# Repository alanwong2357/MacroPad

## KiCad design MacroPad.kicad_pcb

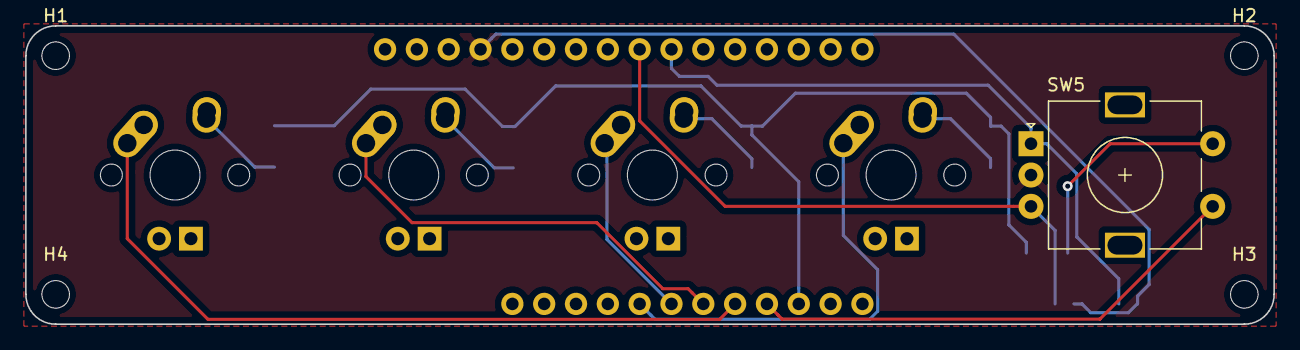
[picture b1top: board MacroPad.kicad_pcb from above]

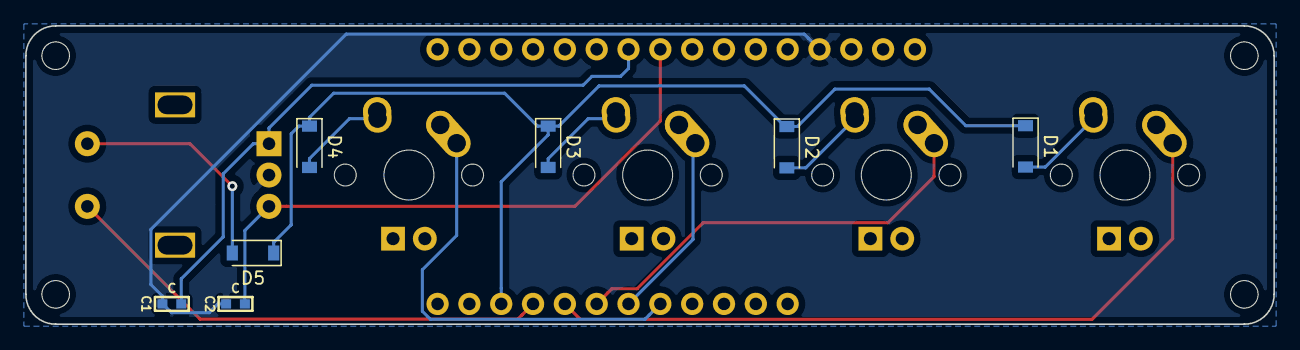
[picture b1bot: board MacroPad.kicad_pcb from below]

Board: 2 copper layers, 99.6 x 23.8 mm, 17 parts (8 on the bottom side), 14 nets.

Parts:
C1, C2: C; C_0603
D1, D2, D3, D4, D5: D; D_SOD-123
H1, H2, H3, H4: MountingHole; MountingHole_2.2mm_M2
MS1: FEATHERWING_NODIM
SW1, SW2, SW3, SW4: SW_Push; MX-1U
SW5: Rotary_Encoder_Switch; RotaryEncoder_Alps_EC11E-Switch_Vertical_H20mm

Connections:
Col1: MS1.20, SW5.S1
Col2: MS1.21, SW1.1
Col3: MS1.22, SW2.1
Col4: MS1.23, SW3.1
Col5: MS1.24, SW4.1
GND: C1.1, C2.1, MS1.4, SW5.C
unnamed: D1.2, SW1.2
unnamed: D2.2, SW2.2
unnamed: D3.2, SW3.2
unnamed: D4.2, SW4.2
unnamed: D5.2, SW5.S2
RotA: C1.2, MS1.10, SW5.A
RotB: C2.2, MS1.9, SW5.B
Row1: D1.1, D2.1, D3.1, D4.1, D5.1, MS1.19

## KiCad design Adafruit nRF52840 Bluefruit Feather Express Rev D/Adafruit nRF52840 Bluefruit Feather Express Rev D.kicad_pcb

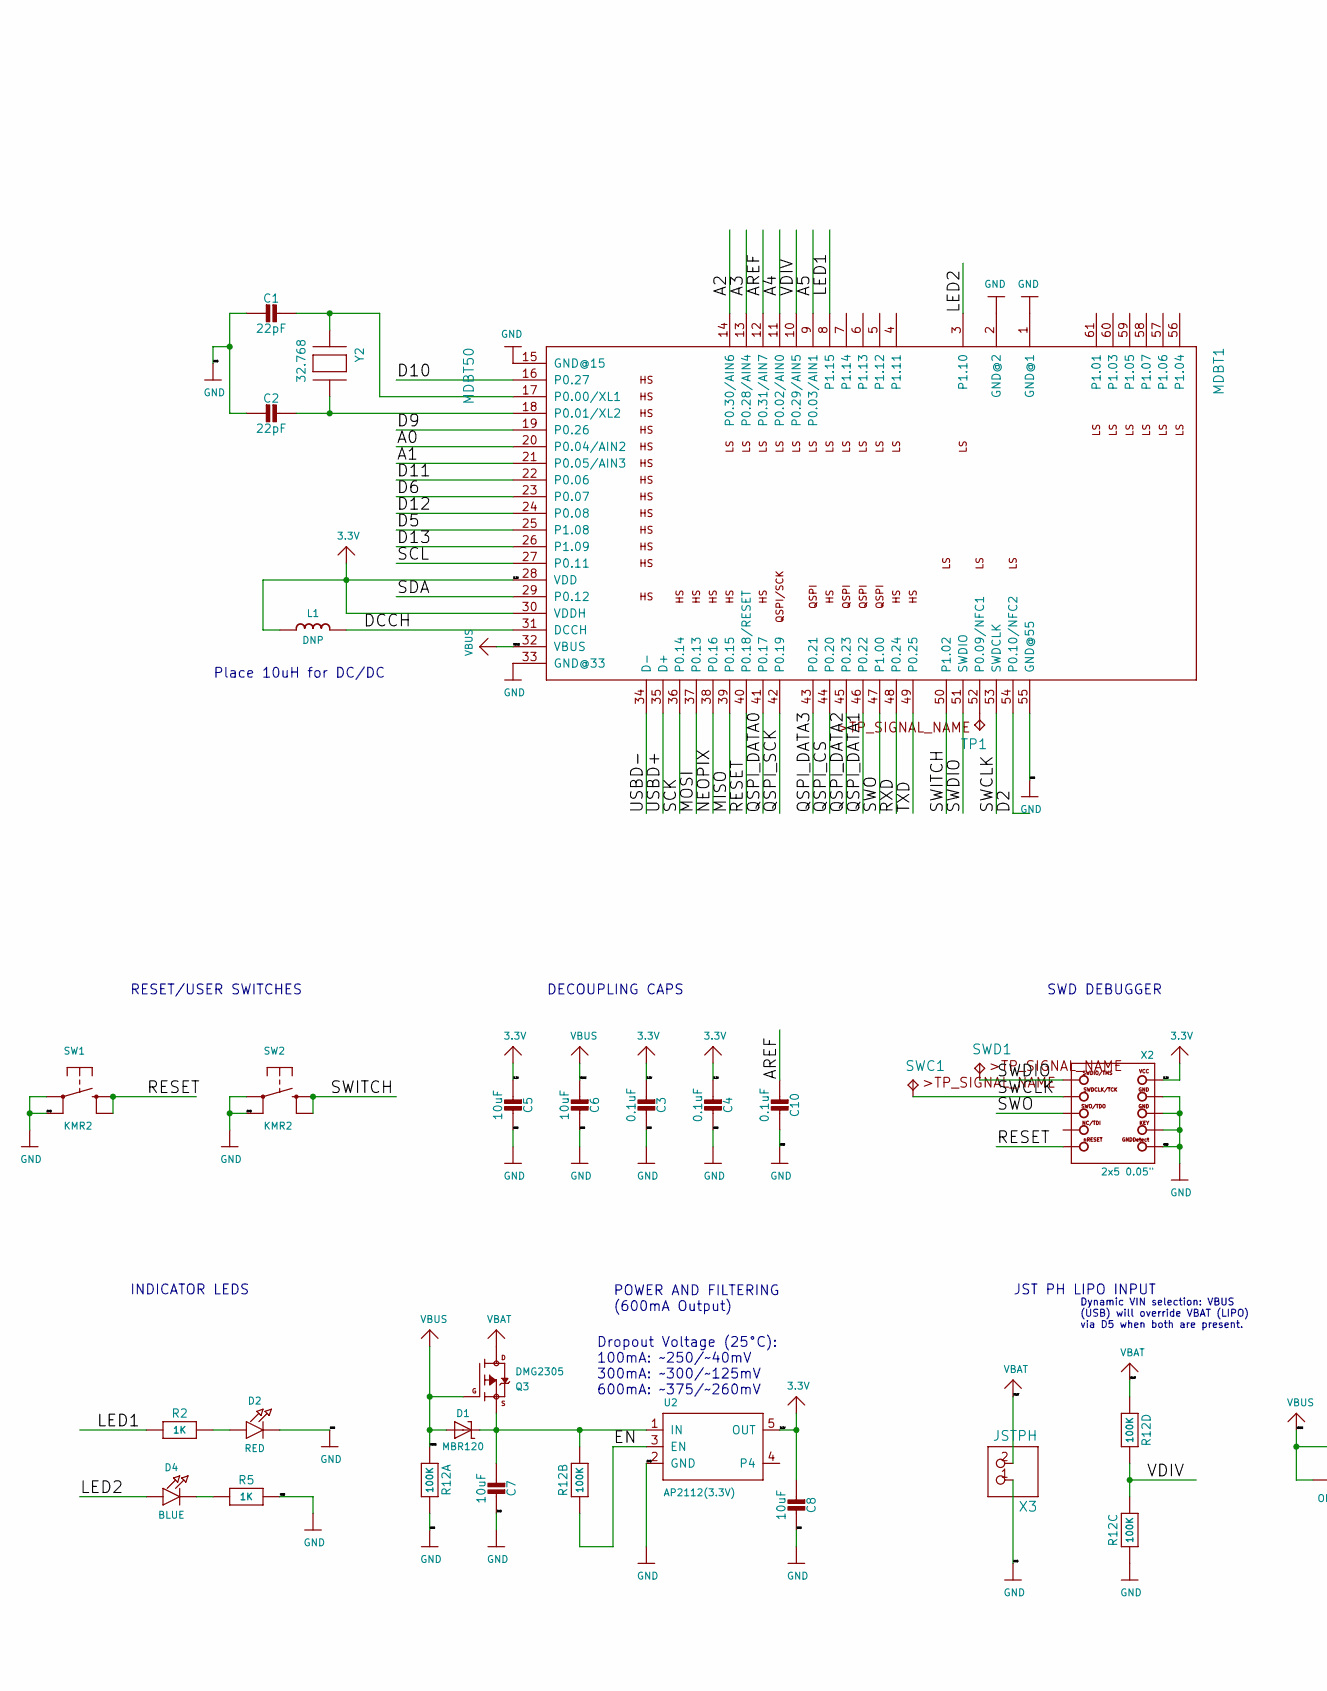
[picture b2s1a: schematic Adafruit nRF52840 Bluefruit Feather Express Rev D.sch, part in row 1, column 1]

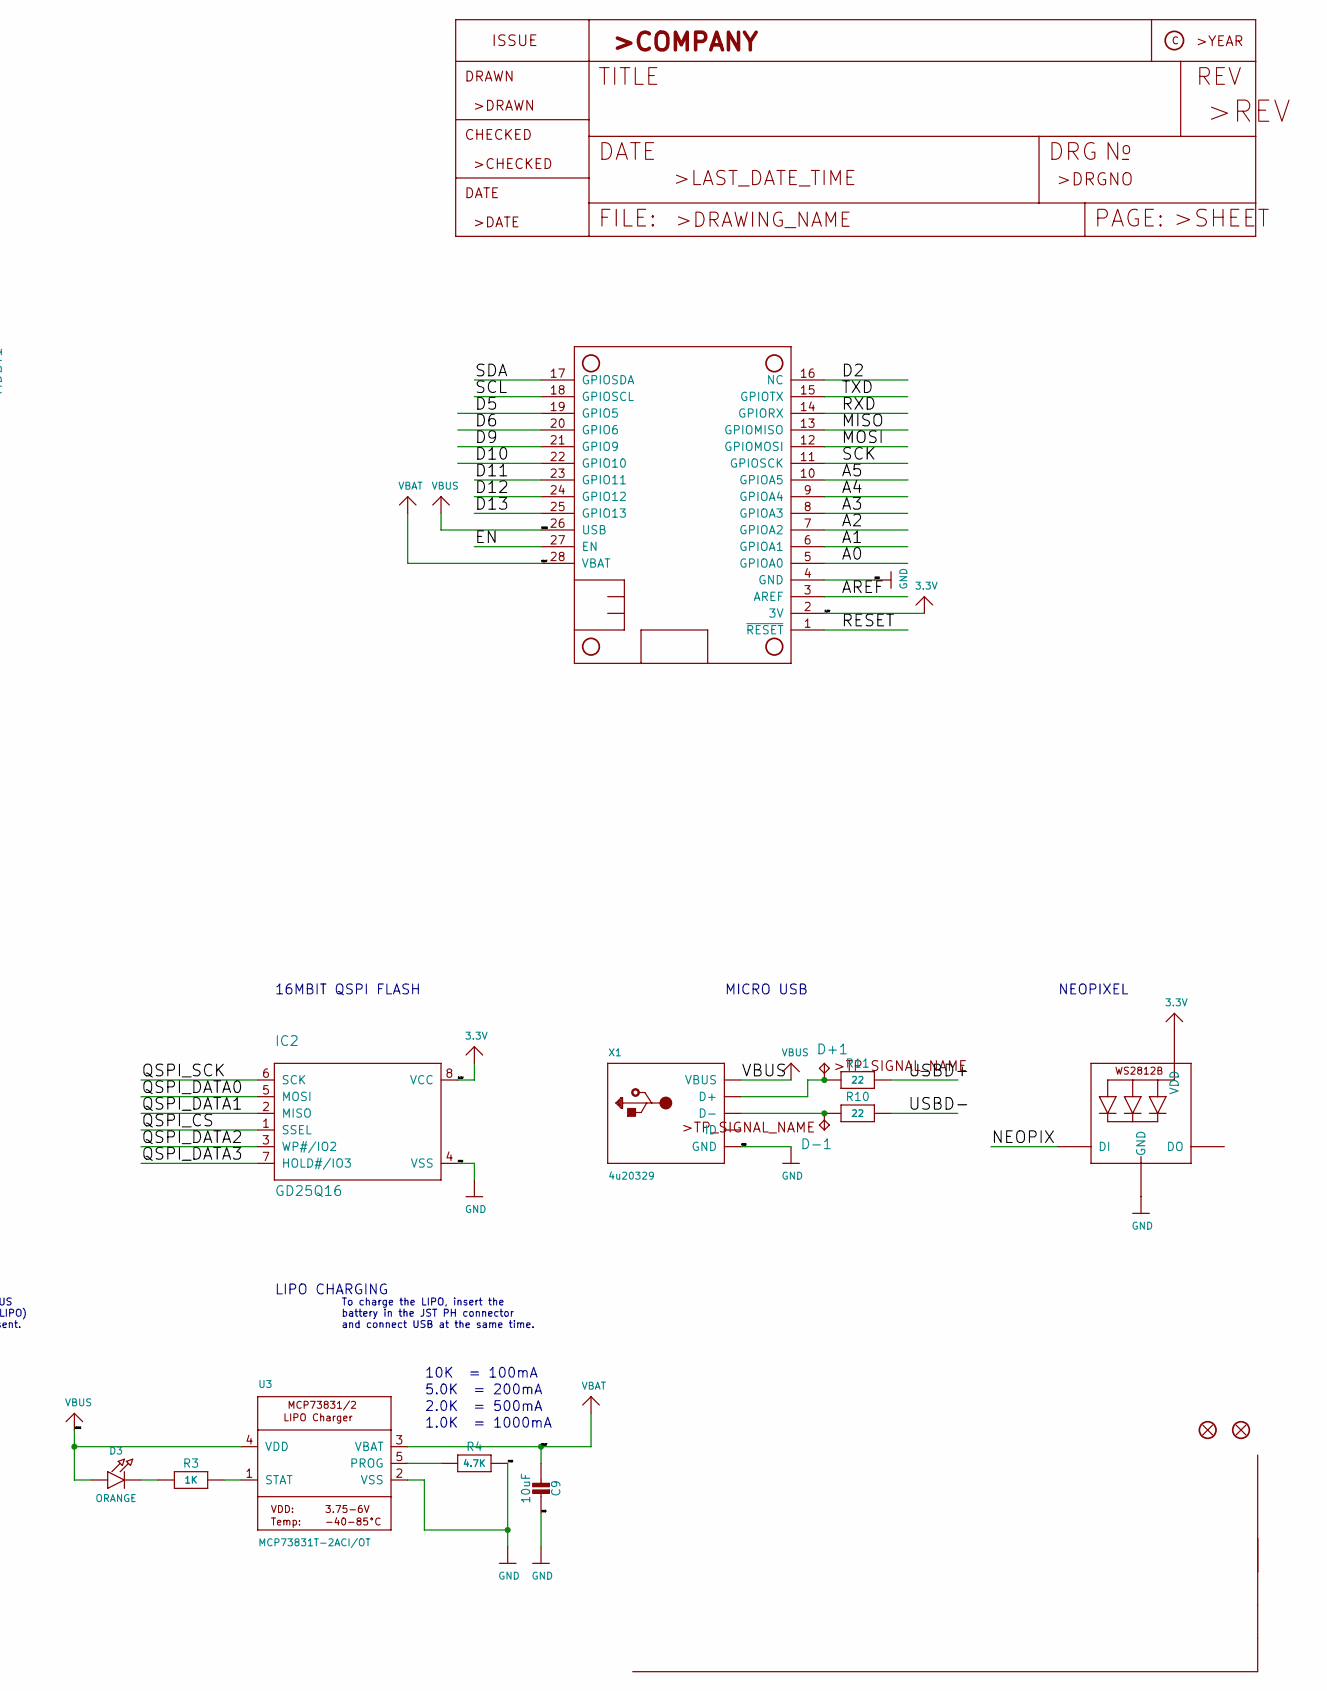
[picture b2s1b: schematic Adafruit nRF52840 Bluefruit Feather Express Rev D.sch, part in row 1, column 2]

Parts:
C1, C2: 22pF; 0603-NO
C3, C4, C10: 0.1uF; 0603-NO
C5, C6, C7, C8, C9: 10uF; 0805-NO
D1: MBR120; SOD-123
D2: RED; CHIPLED_0805_NOOUTLINE
D3: ORANGE; CHIPLED_0805_NOOUTLINE
D4: BLUE; CHIPLED_0805_NOOUTLINE
D+1: TPTP10R; TP10R
D-1: TPTP10R; TP10R
FID1, FID2: FIDUCIAL_1MM
IC2: GD25Q16; USON8
L1: DNP; _0805MP
LED1: WS2812B3535; LED3535
MDBT1: MDBT50
MS1: FEATHERWING_NODIM
Q3: DMG2305; SOT23-R
R2, R3, R5: 1K; 0603-NO
R4: 4.7K; 0603-NO
R10, R11: 22; 0603-NO
R12: 100K; RESPACK_4X0603
SW1, SW2: KMR2; BTN_KMR2_4.6X2.8
SWC1: TPTP12R; TP12R
SWD1: TPTP12R; TP12R
TP1: TPTP10R; TP10R
U2: AP2112(3.3V); SOT23-5
U3: MCP73831T-2ACI/OT; SOT23-5
X1: 4u20329; 4UCONN_20329_V2
X2: 2x5 0.05\"; 2X05_1.27MM_BOX_POSTS
X3: JSTPH; JSTPH2
Y2: 32.768; XTAL3215

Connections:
3.3V: C3.2, C4.2, C5.2, C8.2, IC2.8 (VCC), L1.1, LED1.2 (VDD), MDBT1.28 (VDD), MDBT1.30 (VDDH), MS1.2 (3V), U2.5 (OUT), X2.1 (VCC)
/A0: MDBT1.20 (P0.04/AIN2), MS1.5 (GPIOA0)
/A1: MDBT1.21 (P0.05/AIN3), MS1.6 (GPIOA1)
/A2: MDBT1.14 (P0.30/AIN6), MS1.7 (GPIOA2)
/A3: MDBT1.13 (P0.28/AIN4), MS1.8 (GPIOA3)
/A4: MDBT1.11 (P0.02/AIN0), MS1.9 (GPIOA4)
/A5: MDBT1.9 (P0.03/AIN1), MS1.10 (GPIOA5)
/AREF: C10.2, MDBT1.12 (P0.31/AIN7), MS1.3 (AREF)
/D2: MDBT1.54 (P0.10/NFC2), MS1.16 (NC)
/D5: MDBT1.25 (P1.08), MS1.19 (GPIO5)
/D6: MDBT1.23 (P0.07), MS1.20 (GPIO6)
/D9: MDBT1.19 (P0.26), MS1.21 (GPIO9)
/D10: MDBT1.16 (P0.27), MS1.22 (GPIO10)
/D11: MDBT1.22 (P0.06), MS1.23 (GPIO11)
/D12: MDBT1.24 (P0.08), MS1.24 (GPIO12)
/D13: MDBT1.26 (P1.09), MS1.25 (GPIO13)
/DCCH: L1.2, MDBT1.31 (DCCH)
/EN: MS1.27 (EN), R12.2 (1), U2.3 (EN)
/LED1: MDBT1.8 (P1.15), R2.1
/LED2: D4.A, MDBT1.3 (P1.10)
/MISO: MDBT1.39 (P0.15), MS1.13 (GPIOMISO)
/MOSI: MDBT1.37 (P0.13), MS1.12 (GPIOMOSI)
/NEOPIX: LED1.1 (DI), MDBT1.38 (P0.16)
/QSPI_CS: IC2.1 (SSEL), MDBT1.44 (P0.20)
/QSPI_DATA0: IC2.5 (MOSI), MDBT1.41 (P0.17)
/QSPI_DATA1: IC2.2 (MISO), MDBT1.46 (P0.22)
/QSPI_DATA2: IC2.3 (WP#/IO2), MDBT1.45 (P0.23)
/QSPI_DATA3: IC2.7 (HOLD#/IO3), MDBT1.43 (P0.21)
/QSPI_SCK: IC2.6 (SCK), MDBT1.42 (P0.19)
/RESET: MDBT1.40 (P0.18/RESET), MS1.1 (~RESET), SW1.B (S), SW1.B' (S1), X2.10 (NRESET)
/RXD: MDBT1.48 (P0.24), MS1.14 (GPIORX)
/SCK: MDBT1.36 (P0.14), MS1.11 (GPIOSCK)
/SCL: MDBT1.27 (P0.11), MS1.18 (GPIOSCL)
/SDA: MDBT1.29 (P0.12), MS1.17 (GPIOSDA)
/SWCLK: MDBT1.53 (SWDCLK), SWC1.TP, X2.4 (SWDCLK)
/SWDIO: MDBT1.51 (SWDIO), SWD1.TP, X2.2 (SWDIO)
/SWITCH: MDBT1.50 (P1.02), SW2.B (S), SW2.B' (S1)
/SWO: MDBT1.47 (P1.00), X2.6 (SWO)
/TXD: MDBT1.49 (P0.25), MS1.15 (GPIOTX)
/USBD+: MDBT1.35 (D+), R11.2
/USBD-: MDBT1.34 (D-), R10.2
/VDIV: MDBT1.10 (P0.29/AIN5), R12.5 (2), R12.6 (2)
GND: C1.2, C2.2, C3.1, C4.1, C5.1, C6.1, C7.1, C8.1, C9.1, C10.1, D2.C, IC2.4 (VSS), LED1.4 (GND), MDBT1.1 (GND@1), MDBT1.2 (GND@2), MDBT1.15 (GND@15), MDBT1.33 (GND@33), MDBT1.55 (GND@55), MS1.4 (GND), R4.2, R5.2, R12.3 (1), R12.8 (2), SW1.A, SW1.A' (P1), SW2.A, SW2.A' (P1), U2.2 (GND), U3.2 (VSS), X1.BASE@1 (GND), X1.BASE@2 (GND), X1.GND, X1.SPRT@1 (GND), X1.SPRT@2 (GND), X1.SPRT@3 (GND), X1.SPRT@4 (GND), X2.3 (GND@1), X2.5 (GND@2), X2.7 (KEY), X2.9 (GNDDETECT), X3.1
unnamed: C1.1, MDBT1.17 (P0.00/XL1), Y2.P$1
unnamed: C2.1, MDBT1.18 (P0.01/XL2), Y2.P$2
unnamed: C7.2, D1.C, Q3.2 (S), R12.7 (2), U2.1 (IN)
unnamed: D2.A, R2.2
unnamed: D3.C, R3.1
unnamed: D4.C, R5.1
unnamed: D+1.TP, R11.1, X1.D+
unnamed: D-1.TP, R10.1, X1.D-
unnamed: MDBT1.52 (P0.09/NFC1), TP1.TP
unnamed: R3.2, U3.1 (STAT)
unnamed: R4.1, U3.5 (PROG)
VBAT: C9.2, MS1.28 (VBAT), Q3.3 (D), R12.4 (1), U3.3 (VBAT), X3.2
VBUS: C6.2, D1.A, D3.A, MDBT1.32 (VBUS), MS1.26 (USB), Q3.1 (G), R12.1, U3.4 (VDD), X1.VBUS

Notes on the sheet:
10K = 100mA
5.0K = 200mA
2.0K = 500mA
1.0K = 1000mA
LIPO CHARGING
To charge the LIPO, insert the battery in the JST PH connector and connect USB at the same time.
POWER AND FILTERING (600mA Output)
JST PH LIPO INPUT
Dynamic VIN selection: VBUS (USB) will override VBAT (LIPO) via D5 when both are present.
Dropout Voltage (25°C): 100mA: ~~250/~~40mV 300mA: ~~300/~~125mV 600mA: ~~375/~~260mV
INDICATOR LEDS
RESET/USER SWITCHES
DECOUPLING CAPS
SWD DEBUGGER
16MBIT QSPI FLASH
MICRO USB
NEOPIXEL
Place 10uH for DC/DC

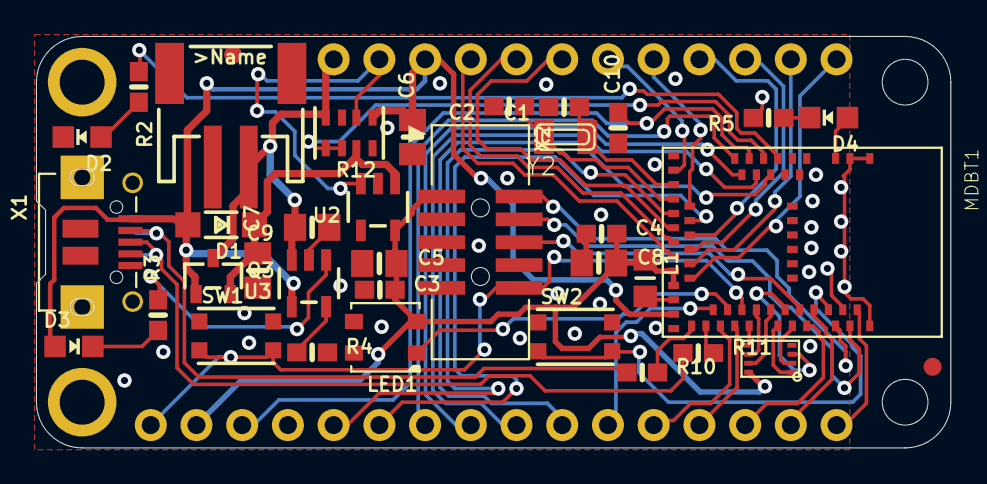
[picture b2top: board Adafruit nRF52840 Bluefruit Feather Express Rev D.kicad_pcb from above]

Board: 4 copper layers, 50.8 x 22.9 mm, 45 parts (0 on the bottom side), 56 nets.

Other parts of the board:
U$10: PCBFEAT-REV-056
U$12: NRF52840_BOT
U$14: NRF52840_TOP
